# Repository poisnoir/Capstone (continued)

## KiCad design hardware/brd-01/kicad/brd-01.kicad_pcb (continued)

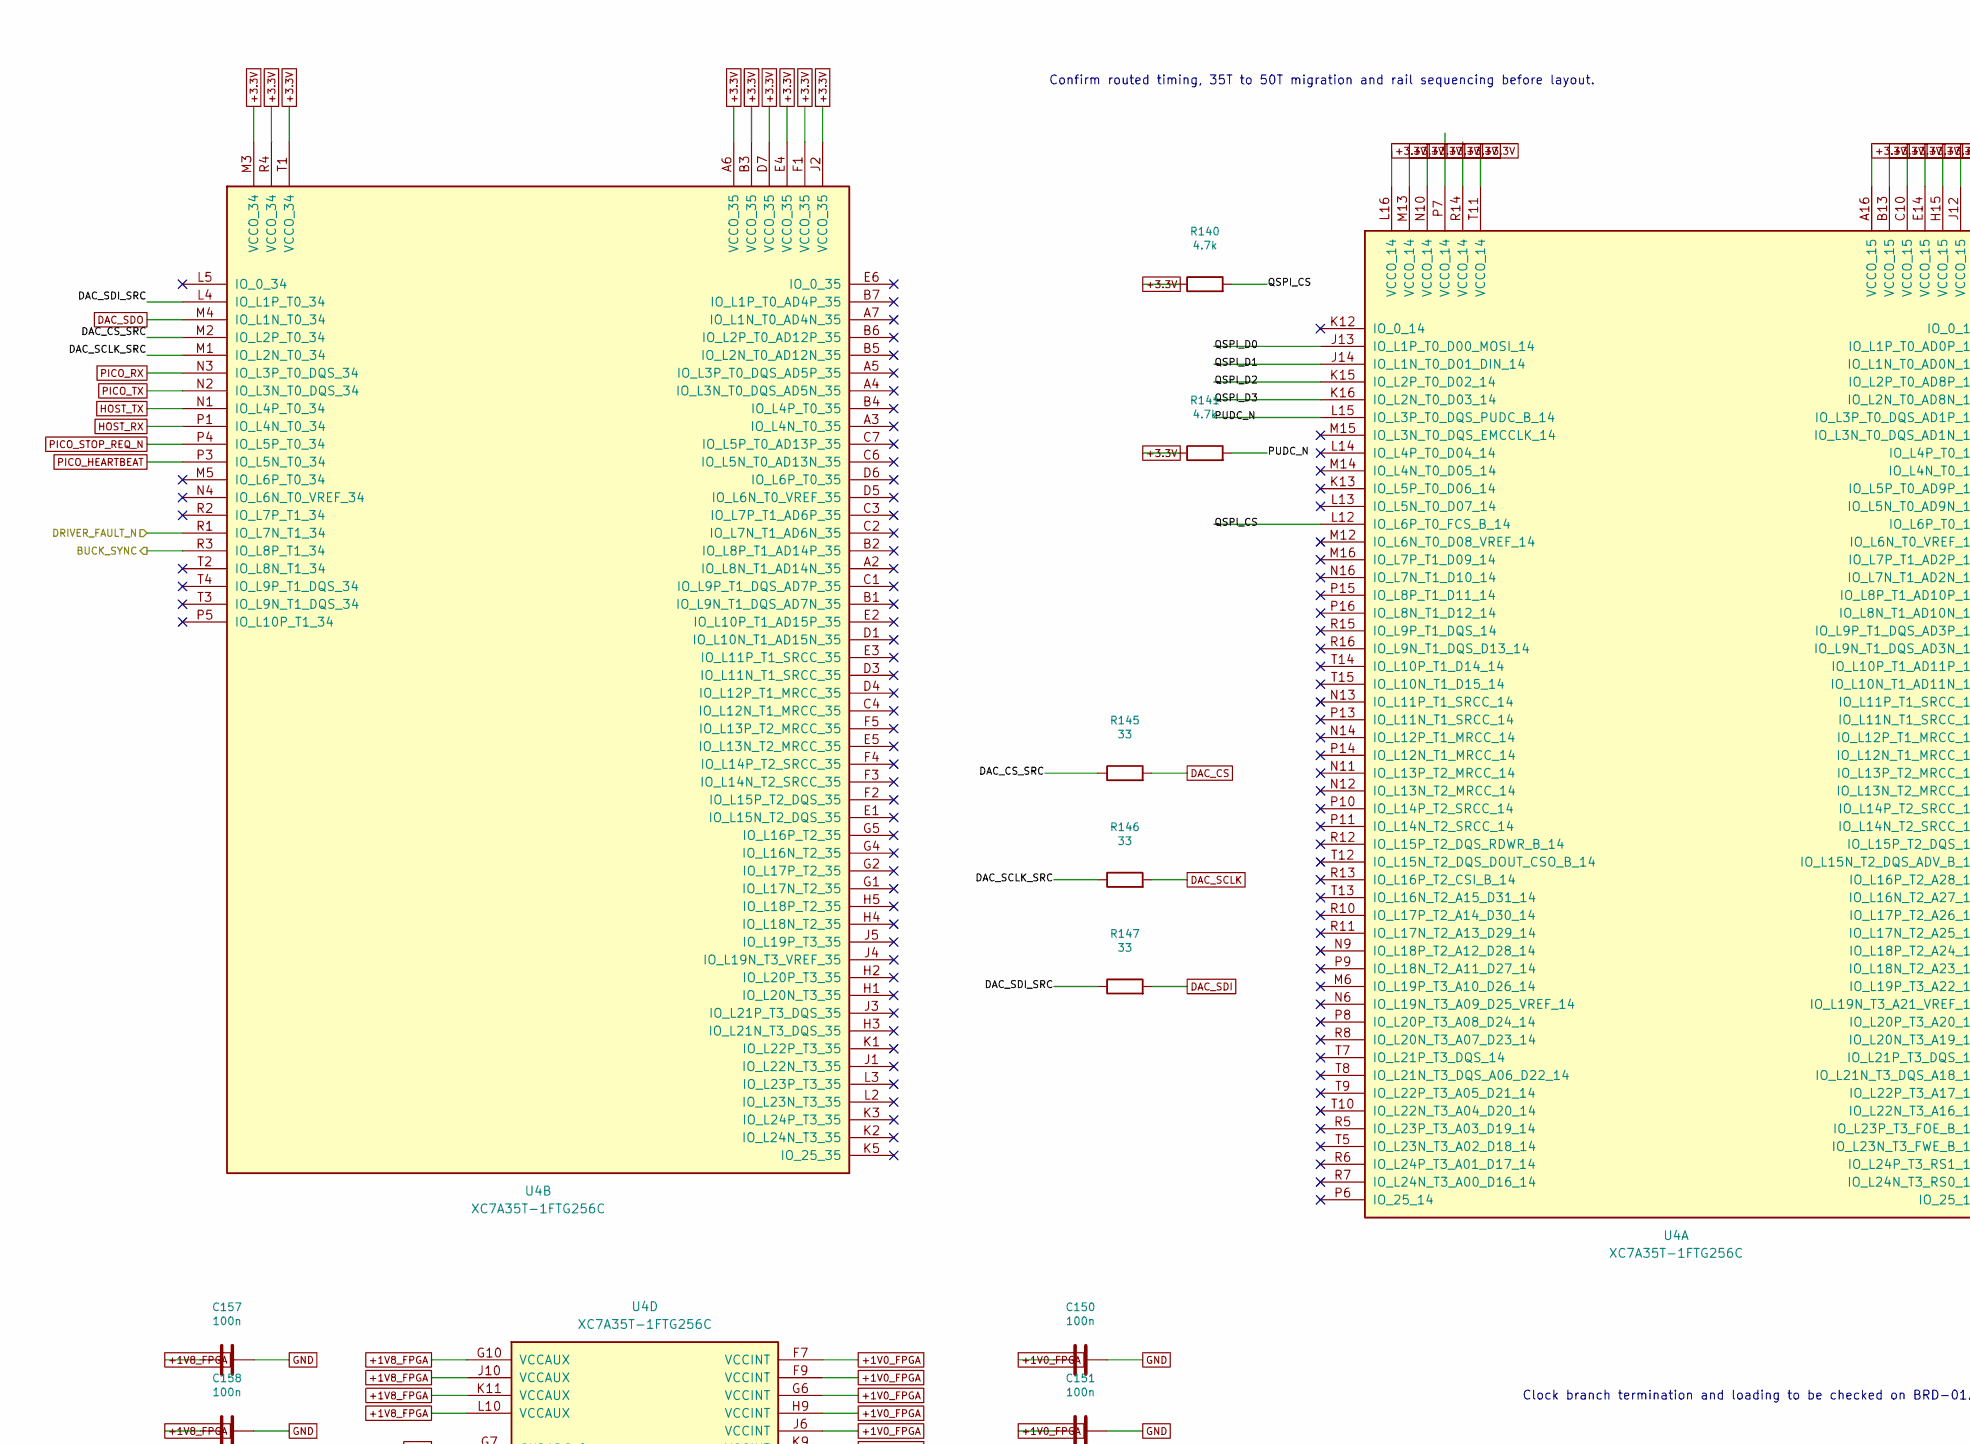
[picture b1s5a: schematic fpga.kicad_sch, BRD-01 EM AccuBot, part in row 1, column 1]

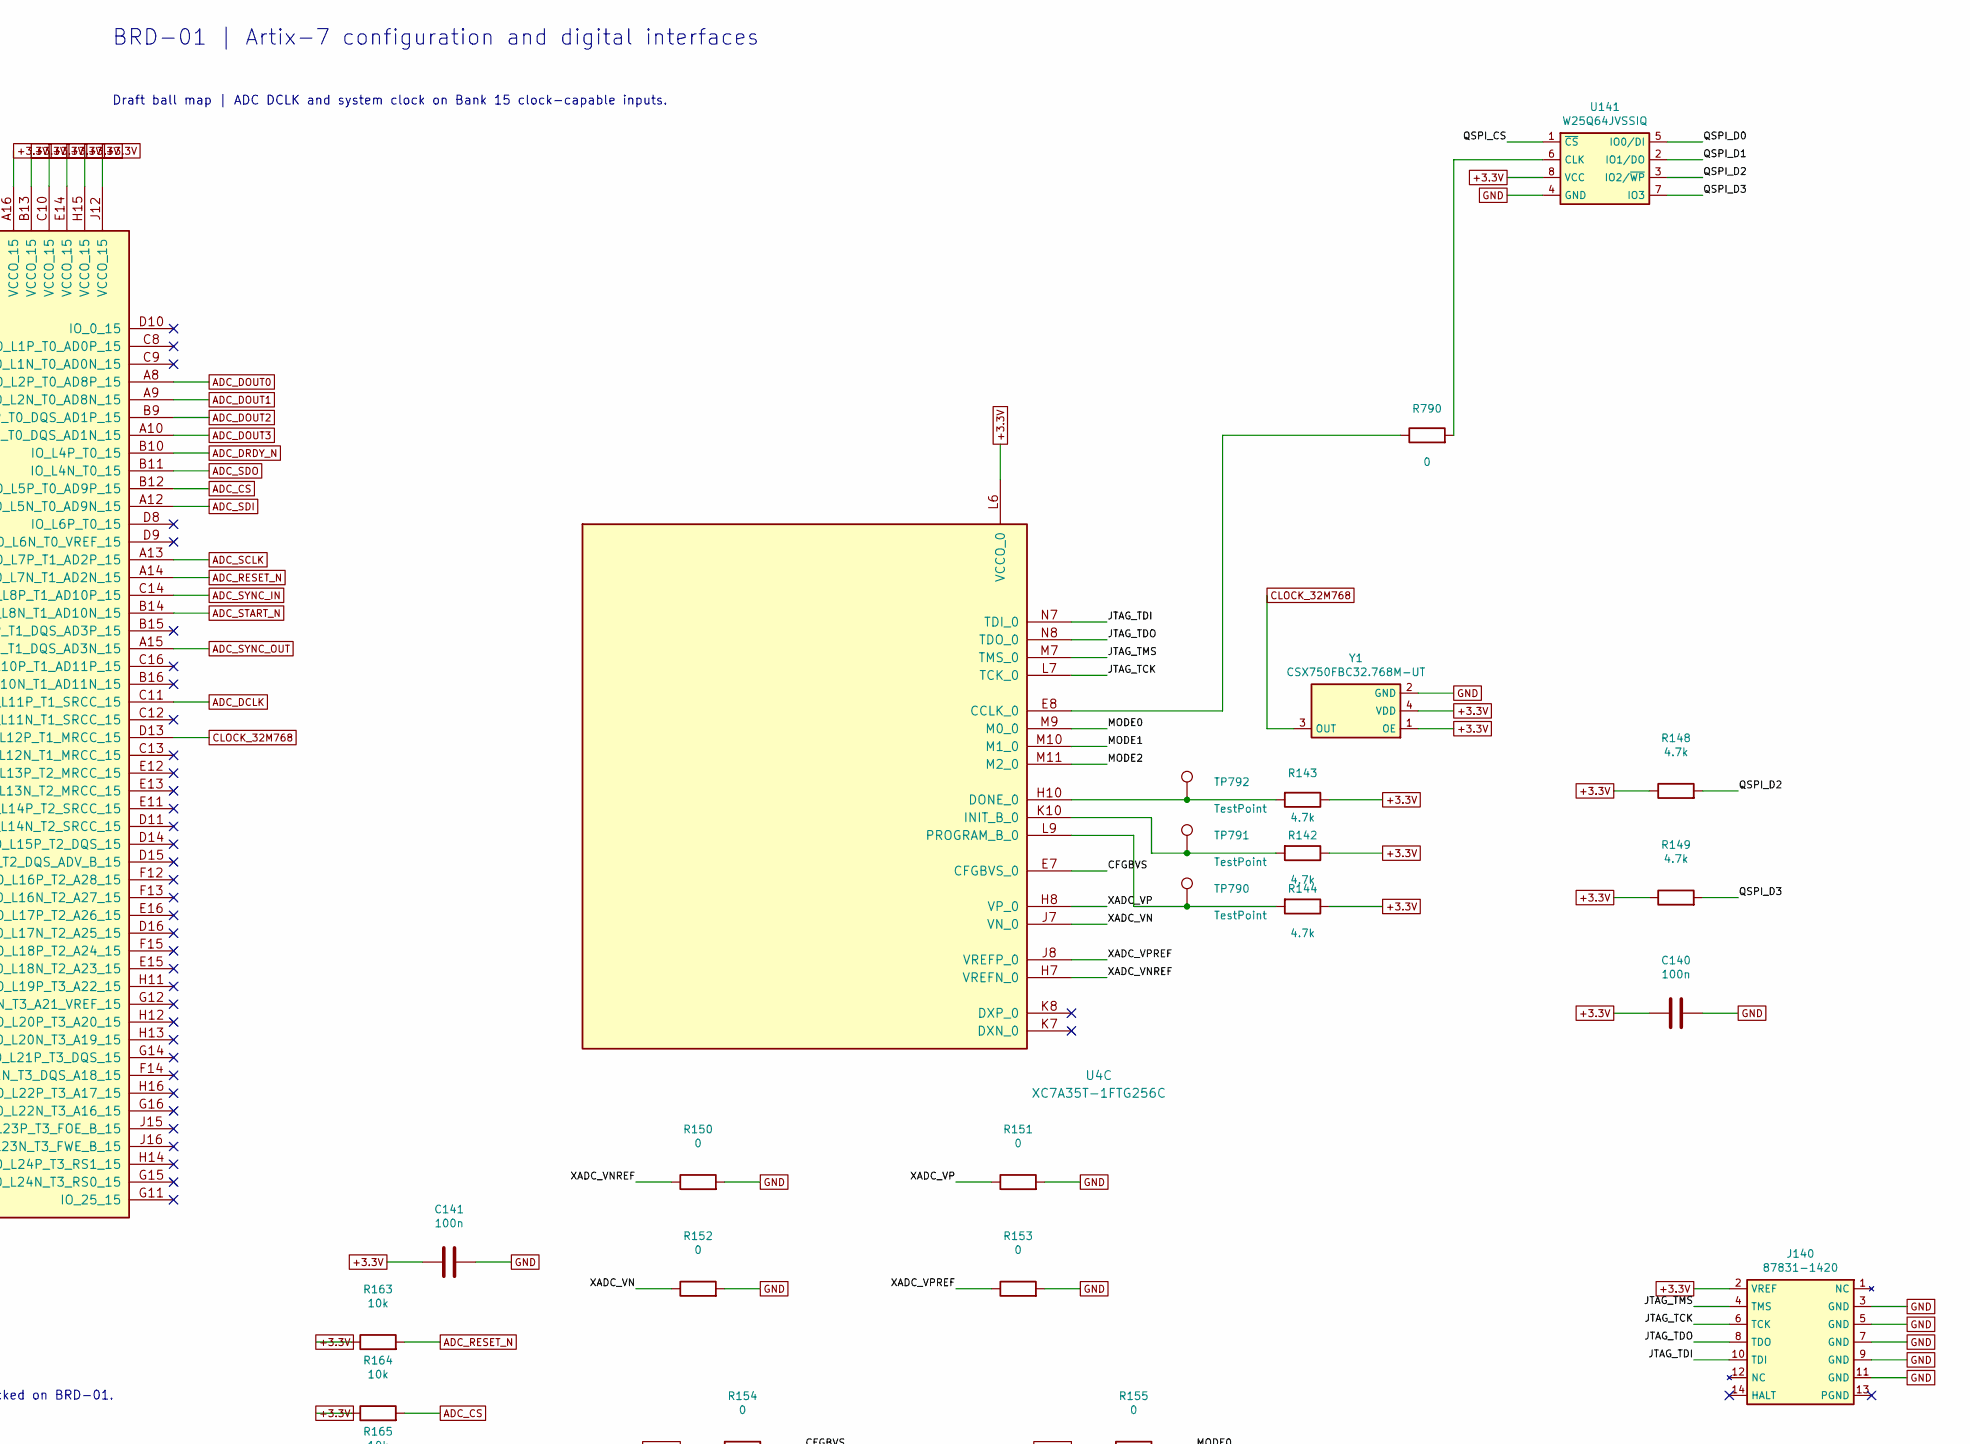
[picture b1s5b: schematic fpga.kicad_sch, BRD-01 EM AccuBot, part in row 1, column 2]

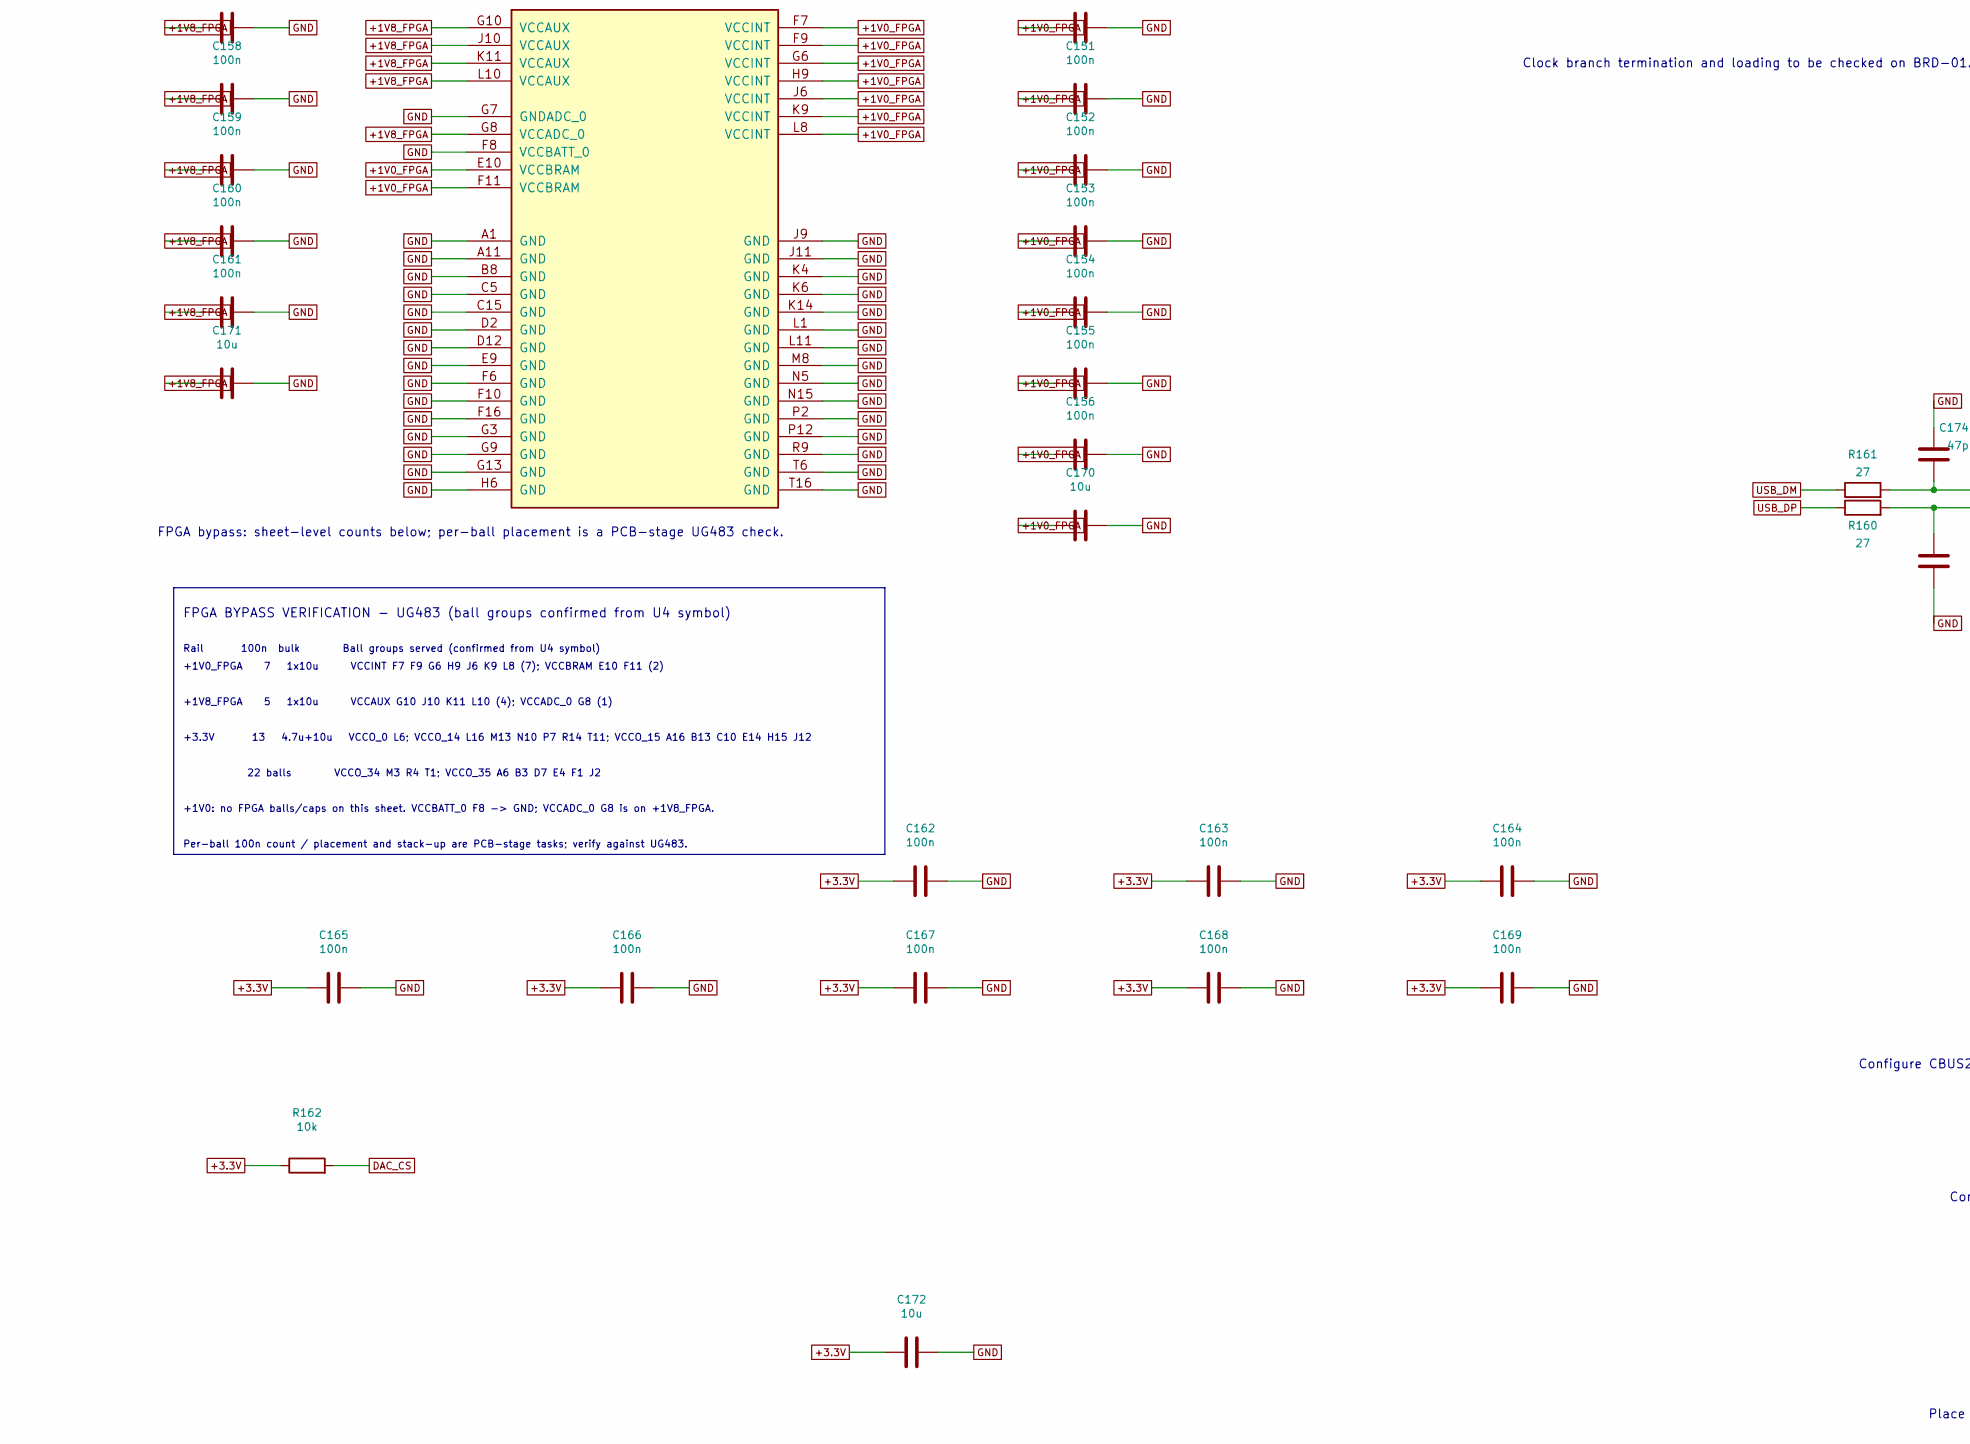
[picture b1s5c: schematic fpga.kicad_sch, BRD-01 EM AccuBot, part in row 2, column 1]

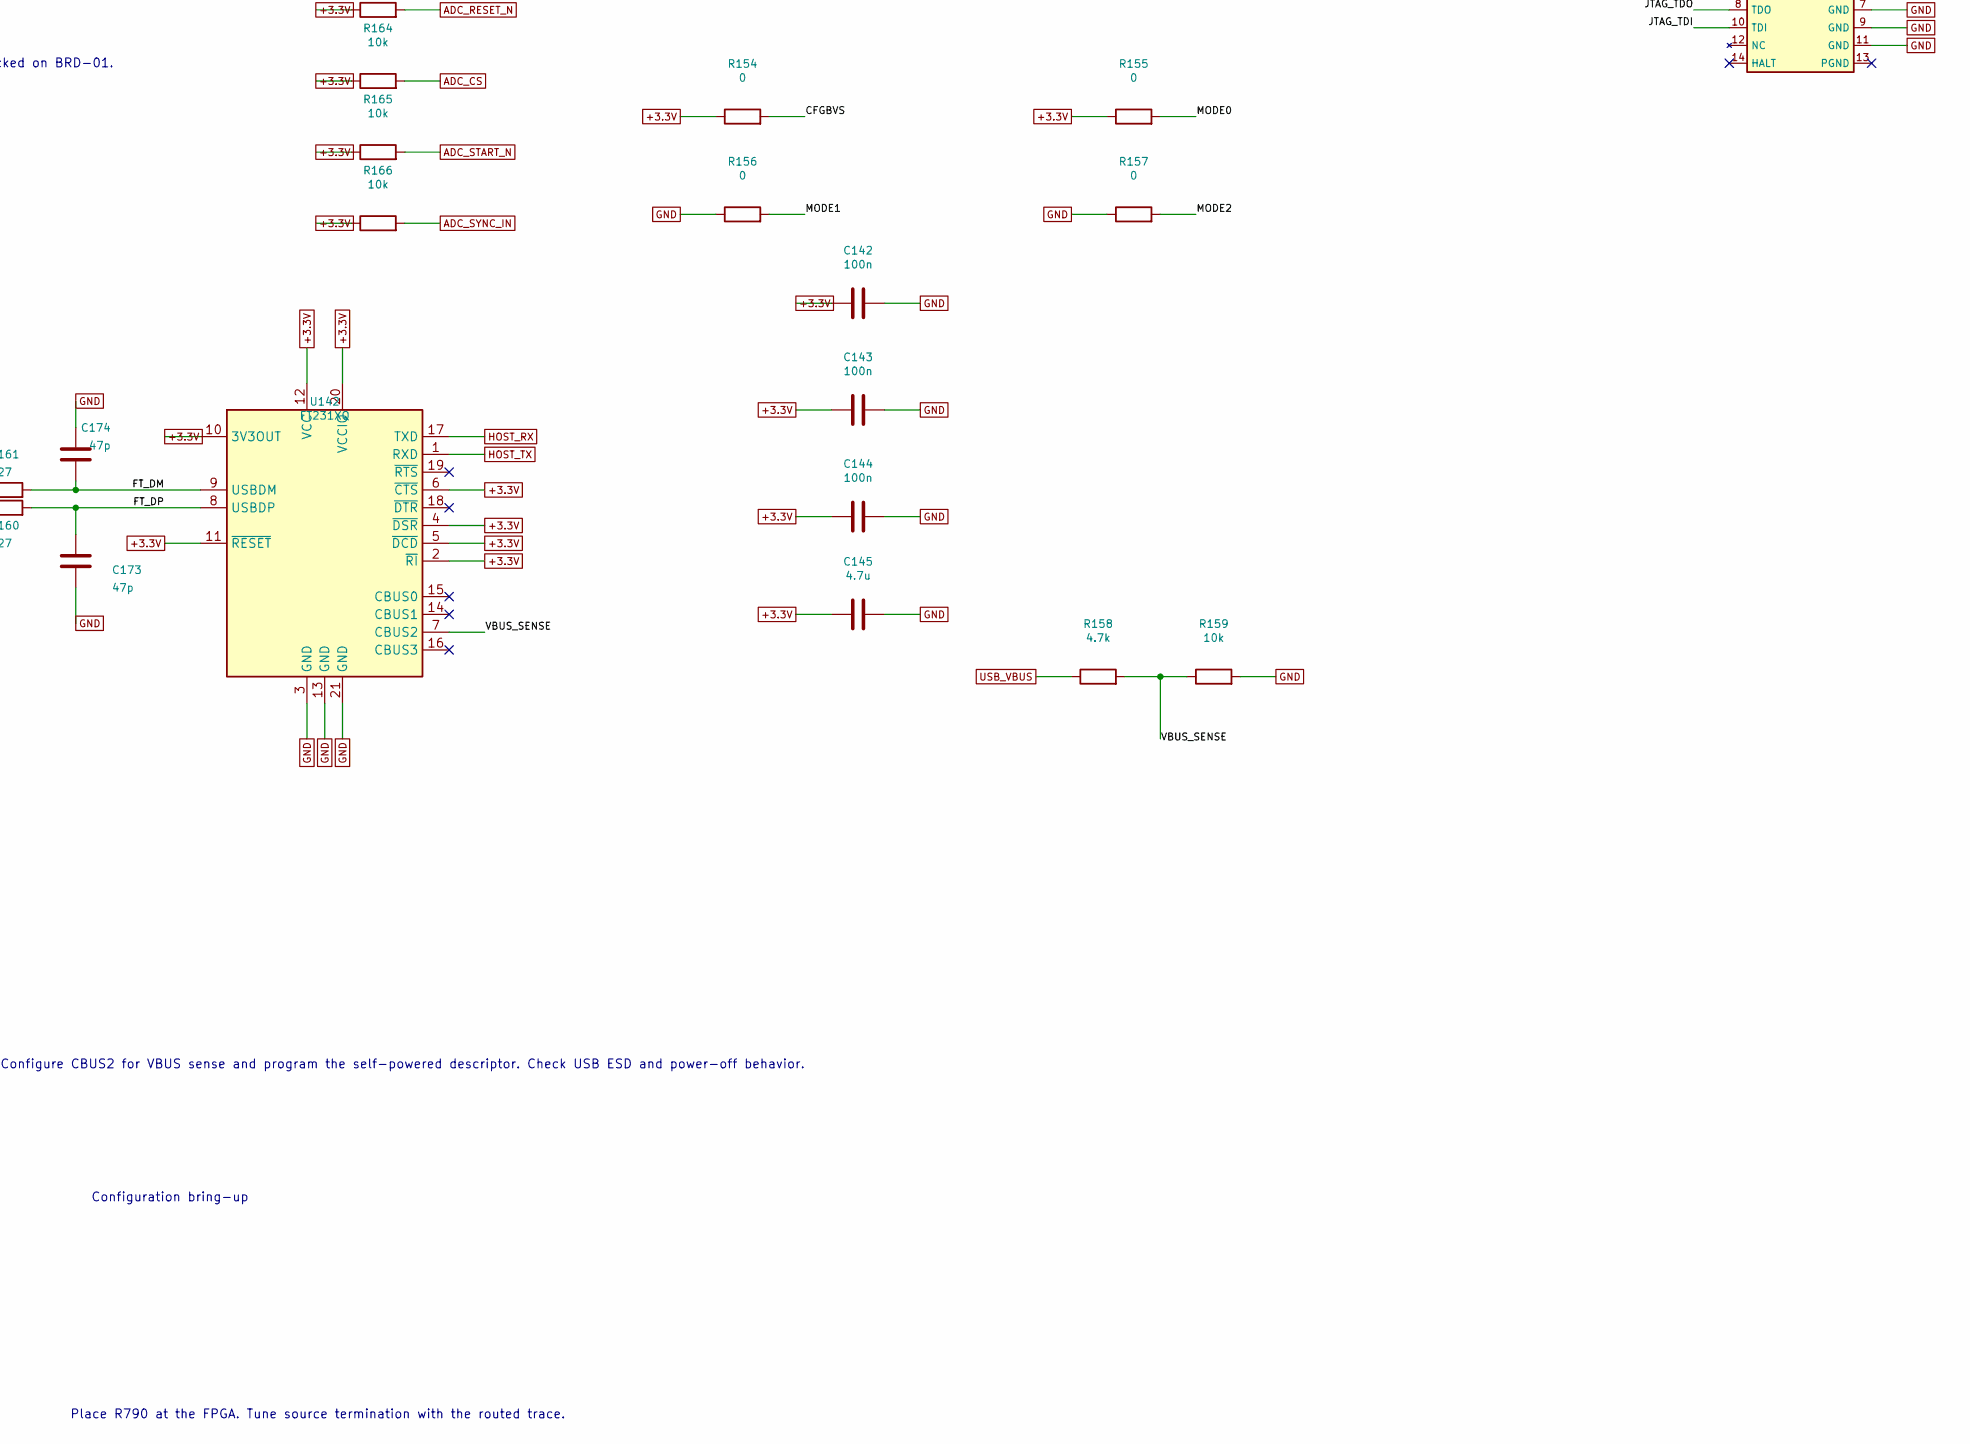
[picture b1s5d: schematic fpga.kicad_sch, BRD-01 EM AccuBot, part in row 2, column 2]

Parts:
C140, C141, C142, C143, C144, C150, C151, C152, C153, C154, C155, C156, C157, C158, C159, C160, C161, C162, C163, C164, C165, C166, C167, C168, C169: 100n; C_0603_1608Metric
C145: 4.7u; C_0805_2012Metric
C170, C171, C172: 10u; C_0805_2012Metric
C173, C174: 47p; C_0603_1608Metric
J140: 87831-1420; Molex_87831-1420
R140, R141, R142, R143, R144, R148, R149, R158: 4.7k; R_0603_1608Metric
R145, R146, R147: 33; R_0603_1608Metric
R150, R151, R152, R153, R154, R155, R156, R157, R790: 0; R_0603_1608Metric
R159, R162, R163, R164, R165, R166: 10k; R_0603_1608Metric
R160, R161: 27; R_0603_1608Metric
TP790, TP791, TP792: TestPoint; TestPoint_Pad_D1.5mm
U4: XC7A35T-1FTG256C; Xilinx_FTG256
U141: W25Q64JVSSIQ; SOIC-8_5.3x5.3mm_P1.27mm
U142: FT231XQ; QFN-20-1EP_4x4mm_P0.5mm_EP2.5x2.5mm
Y1: CSX750FBC32.768M-UT; Oscillator_SMD_SeikoEpson_SG8002CA-4Pin_7.0x5.0mm

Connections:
+1V0_FPGA: C150.1, C151.1, C152.1, C153.1, C154.1, C155.1, C156.1, C170.1, U4.E10 (VCCBRAM), U4.F7 (VCCINT), U4.F9 (VCCINT), U4.F11 (VCCBRAM), U4.G6 (VCCINT), U4.H9 (VCCINT), U4.J6 (VCCINT), U4.K9 (VCCINT), U4.L8 (VCCINT); also elsewhere on the board
+1V8_FPGA: C157.1, C158.1, C159.1, C160.1, C161.1, C171.1, U4.G8 (VCCADC_0), U4.G10 (VCCAUX), U4.J10 (VCCAUX), U4.K11 (VCCAUX), U4.L10 (VCCAUX); also elsewhere on the board
+3.3V: C140.1, C141.1, C142.1, C143.1, C144.1, C145.1, C162.1, C163.1, C164.1, C165.1, C166.1, C167.1, C168.1, C169.1, C172.1, J140.2 (VREF), R140.1, R141.1, R142.1, R143.1, R144.1, R148.1, R149.1, R154.1, R155.1, R162.1, R163.1, R164.1, R165.1, R166.1, U4.A6 (VCCO_35), U4.A16 (VCCO_15), U4.B3 (VCCO_35), U4.B13 (VCCO_15), U4.C10 (VCCO_15), U4.D7 (VCCO_35), U4.E4 (VCCO_35), U4.E14 (VCCO_15), U4.F1 (VCCO_35), U4.H15 (VCCO_15), U4.J2 (VCCO_35), U4.J12 (VCCO_15), U4.L6 (VCCO_0), U4.L16 (VCCO_14), U4.M3 (VCCO_34), U4.M13 (VCCO_14), U4.N10 (VCCO_14), U4.P7 (VCCO_14), U4.R4 (VCCO_34), U4.R14 (VCCO_14), U4.T1 (VCCO_34), U4.T11 (VCCO_14), U141.8 (VCC), U142.2 (~RI), U142.4 (~DSR), U142.5 (~DCD), U142.6 (~CTS), U142.10 (3V3OUT), U142.11 (~RESET), U142.12 (VCC), U142.20 (VCCIO), Y1.1 (OE), Y1.4 (VDD); also elsewhere on the board
/BUCK_SYNC: U4.R3 (IO_L8P_T1_34); also elsewhere on the board
/DRIVER_FAULT_N: U4.R1 (IO_L7N_T1_34); also elsewhere on the board
/fpga/CFGBVS: R154.2, U4.E7 (CFGBVS_0)
/fpga/DAC_CS_SRC: R145.1, U4.M2 (IO_L2P_T0_34)
/fpga/DAC_SCLK_SRC: R146.1, U4.M1 (IO_L2N_T0_34)
/fpga/DAC_SDI_SRC: R147.1, U4.L4 (IO_L1P_T0_34)
/fpga/FT_DM: C174.1, R161.2, U142.9 (USBDM)
/fpga/FT_DP: C173.1, R160.2, U142.8 (USBDP)
/fpga/JTAG_TCK: J140.6 (TCK), U4.L7 (TCK_0)
/fpga/JTAG_TDI: J140.10 (TDI), U4.N7 (TDI_0)
/fpga/JTAG_TDO: J140.8 (TDO), U4.N8 (TDO_0)
/fpga/JTAG_TMS: J140.4 (TMS), U4.M7 (TMS_0)
/fpga/MODE0: R155.2, U4.M9 (M0_0)
/fpga/MODE1: R156.2, U4.M10 (M1_0)
/fpga/MODE2: R157.2, U4.M11 (M2_0)
/fpga/PUDC_N: R141.2, U4.L15 (IO_L3P_T0_DQS_PUDC_B_14)
/fpga/QSPI_CS: R140.2, U4.L12 (IO_L6P_T0_FCS_B_14), U141.1 (~CS)
/fpga/QSPI_D0: U4.J13 (IO_L1P_T0_D00_MOSI_14), U141.5 (IO0/DI)
/fpga/QSPI_D1: U4.J14 (IO_L1N_T0_D01_DIN_14), U141.2 (IO1/DO)
/fpga/QSPI_D2: R148.2, U4.K15 (IO_L2P_T0_D02_14), U141.3 (IO2/~WP)
/fpga/QSPI_D3: R149.2, U4.K16 (IO_L2N_T0_D03_14), U141.7 (IO3)
/fpga/VBUS_SENSE: R158.2, R159.1, U142.7 (CBUS2)
/fpga/XADC_VN: R152.1, U4.J7 (VN_0)
/fpga/XADC_VNREF: R150.1, U4.H7 (VREFN_0)
/fpga/XADC_VP: R151.1, U4.H8 (VP_0)
/fpga/XADC_VPREF: R153.1, U4.J8 (VREFP_0)
ADC_CS: R164.2, U4.B12 (IO_L5P_T0_AD9P_15); also elsewhere on the board
ADC_DCLK: U4.C11 (IO_L11P_T1_SRCC_15); also elsewhere on the board
ADC_DOUT0: U4.A8 (IO_L2P_T0_AD8P_15); also elsewhere on the board
ADC_DOUT1: U4.A9 (IO_L2N_T0_AD8N_15); also elsewhere on the board
ADC_DOUT2: U4.B9 (IO_L3P_T0_DQS_AD1P_15); also elsewhere on the board
ADC_DOUT3: U4.A10 (IO_L3N_T0_DQS_AD1N_15); also elsewhere on the board
ADC_DRDY_N: U4.B10 (IO_L4P_T0_15); also elsewhere on the board
ADC_RESET_N: R163.2, U4.A14 (IO_L7N_T1_AD2N_15); also elsewhere on the board
ADC_SCLK: U4.A13 (IO_L7P_T1_AD2P_15); also elsewhere on the board
ADC_SDI: U4.A12 (IO_L5N_T0_AD9N_15); also elsewhere on the board
ADC_SDO: U4.B11 (IO_L4N_T0_15); also elsewhere on the board
ADC_START_N: R165.2, U4.B14 (IO_L8N_T1_AD10N_15); also elsewhere on the board
ADC_SYNC_IN: R166.2, U4.C14 (IO_L8P_T1_AD10P_15); also elsewhere on the board
ADC_SYNC_OUT: U4.A15 (IO_L9N_T1_DQS_AD3N_15); also elsewhere on the board
CLOCK_32M768: U4.D13 (IO_L12P_T1_MRCC_15), Y1.3 (OUT); also elsewhere on the board
DAC_CS: R145.2, R162.2; also elsewhere on the board
DAC_SCLK: R146.2; also elsewhere on the board
DAC_SDI: R147.2; also elsewhere on the board
DAC_SDO: U4.M4 (IO_L1N_T0_34); also elsewhere on the board
GND: C140.2, C141.2, C142.2, C143.2, C144.2, C145.2, C150.2, C151.2, C152.2, C153.2, C154.2, C155.2, C156.2, C157.2, C158.2, C159.2, C160.2, C161.2, C162.2, C163.2, C164.2, C165.2, C166.2, C167.2, C168.2, C169.2, C170.2, C171.2, C172.2, C173.2, C174.2, J140.3 (GND), J140.5 (GND), J140.7 (GND), J140.9 (GND), J140.11 (GND), R150.2, R151.2, R152.2, R153.2, R156.1, R157.1, R159.2, U4.A1 (GND), U4.A11 (GND), U4.B8 (GND), U4.C5 (GND), U4.C15 (GND), U4.D2 (GND), U4.D12 (GND), U4.E9 (GND), U4.F6 (GND), U4.F8 (VCCBATT_0), U4.F10 (GND), U4.F16 (GND), U4.G3 (GND), U4.G7 (GNDADC_0), U4.G9 (GND), U4.G13 (GND), U4.H6 (GND), U4.J9 (GND), U4.J11 (GND), U4.K4 (GND), U4.K6 (GND), U4.K14 (GND), U4.L1 (GND), U4.L11 (GND), U4.M8 (GND), U4.N5 (GND), U4.N15 (GND), U4.P2 (GND), U4.P12 (GND), U4.R9 (GND), U4.T6 (GND), U4.T16 (GND), U141.4 (GND), U142.3 (GND), U142.13 (GND), U142.21 (GND), Y1.2 (GND); also elsewhere on the board
HOST_RX: U4.P1 (IO_L4N_T0_34), U142.17 (TXD)
HOST_TX: U4.N1 (IO_L4P_T0_34), U142.1 (RXD)
unnamed: R790.1, U4.E8 (CCLK_0)
unnamed: R143.2, TP792.1 (1_1), U4.H10 (DONE_0)
unnamed: R142.2, TP791.1 (1_1), U4.K10 (INIT_B_0)
unnamed: R144.2, TP790.1 (1_1), U4.L9 (PROGRAM_B_0)
unnamed: R790.2, U141.6 (CLK)
PICO_HEARTBEAT: U4.P3 (IO_L5N_T0_34); also elsewhere on the board
PICO_RX: U4.N3 (IO_L3P_T0_DQS_34); also elsewhere on the board
PICO_STOP_REQ_N: U4.P4 (IO_L5P_T0_34); also elsewhere on the board
PICO_TX: U4.N2 (IO_L3N_T0_DQS_34); also elsewhere on the board
USB_DM: R161.1; also elsewhere on the board
USB_DP: R160.1; also elsewhere on the board
USB_VBUS: R158.1; also elsewhere on the board

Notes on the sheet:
Per-ball 100n count / placement and stack-up are PCB-stage tasks; verify against UG483.
FPGA BYPASS VERIFICATION - UG483 (ball groups confirmed from U4 symbol)
Draft ball map | ADC DCLK and system clock on Bank 15 clock-capable inputs.
Rail 100n bulk Ball groups served (confirmed from U4 symbol)
BRD-01 | Artix-7 configuration and digital interfaces
+3.3V 13 4.7u+10u VCCO_0 L6; VCCO_14 L16 M13 N10 P7 R14 T11; VCCO_15 A16 B13 C10 E14 H15 J12
FPGA bypass: sheet-level counts below; per-ball placement is a PCB-stage UG483 check.
Configure CBUS2 for VBUS sense and program the self-powered descriptor. Check USB ESD and power-off behavior.
+1V8_FPGA 5 1x10u VCCAUX G10 J10 K11 L10 (4); VCCADC_0 G8 (1)
Place R790 at the FPGA. Tune source termination with the routed trace.
+1V0: no FPGA balls/caps on this sheet. VCCBATT_0 F8 -> GND; VCCADC_0 G8 is on +1V8_FPGA.
Configuration bring-up
Clock branch termination and loading to be checked on BRD-01.
Confirm routed timing, 35T to 50T migration and rail sequencing before layout.
+1V0_FPGA 7 1x10u VCCINT F7 F9 G6 H9 J6 K9 L8 (7); VCCBRAM E10 F11 (2)
22 balls VCCO_34 M3 R4 T1; VCCO_35 A6 B3 D7 E4 F1 J2
